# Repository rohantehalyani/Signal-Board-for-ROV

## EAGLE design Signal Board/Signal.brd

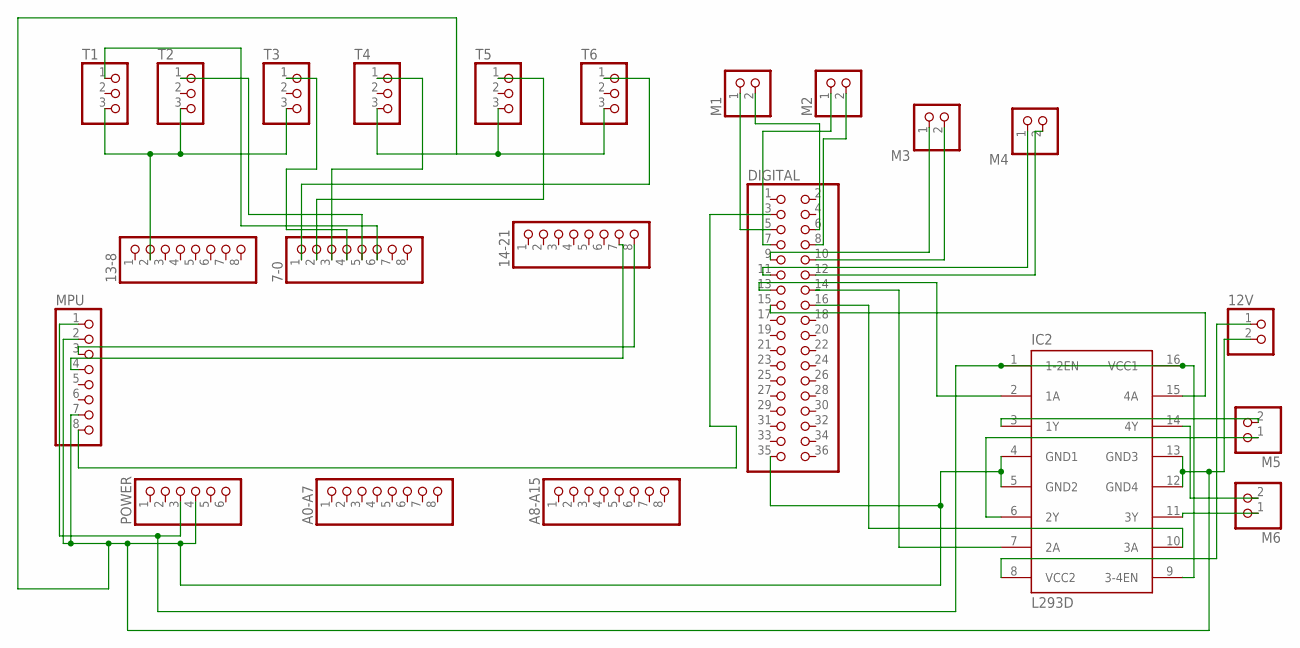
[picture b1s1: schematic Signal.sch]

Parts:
7-0, 13-8, 14-21: PINHD-1X8; 1X08
12V: PINHD-1X2; 1X02
A0-A7, A8-A15: PINHD-1X8; 1X08
DIGITAL: PINHD-2X18; 2X18
IC2: L293D; DIL16
M1, M2, M3, M4, M5, M6: PINHD-1X2; 1X02
MPU: PINHD-1X8; 1X08
POWER: PINHD-1X6; 1X06
T1, T2, T3, T4, T5, T6: PINHD-1X3; 1X03

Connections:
unnamed: DIGITAL.9, M3.1
unnamed: DIGITAL.10, M3.2
unnamed: DIGITAL.8, M2.2
unnamed: 7-0.1, T6.1
unnamed: 7-0.2, T5.1
unnamed: 7-0.3, T4.1
unnamed: 7-0.4, T3.1
unnamed: 7-0.5, T2.1
unnamed: DIGITAL.5, M1.1
unnamed: DIGITAL.6, M1.2
unnamed: DIGITAL.7, M2.1
unnamed: DIGITAL.11, M4.1
unnamed: DIGITAL.12, M4.2
unnamed: 12V.2, DIGITAL.35, IC2.4 (GND1), IC2.5 (GND2), IC2.12 (GND4), IC2.13 (GND3), MPU.2, MPU.7, POWER.4, T4.3, T5.3, T6.3
unnamed: DIGITAL.13, IC2.2 (1A)
unnamed: DIGITAL.14, IC2.7 (2A)
unnamed: DIGITAL.15, IC2.15 (4A)
unnamed: DIGITAL.16, IC2.10 (3A)
unnamed: IC2.1 (1-2EN), IC2.9 (3-4EN), IC2.16 (VCC1), MPU.1, POWER.3
unnamed: DIGITAL.3, MPU.8
unnamed: 7-0.6, T1.1
unnamed: 14-21.8, MPU.3
unnamed: 14-21.7, MPU.4
unnamed: 13-8.2, T1.3, T2.3, T3.3
unnamed: IC2.6 (2Y), M5.1
unnamed: 12V.1, IC2.8 (VCC2)
unnamed: IC2.14 (4Y), M6.2
unnamed: IC2.3 (1Y), M5.2
unnamed: IC2.11 (3Y), M6.1

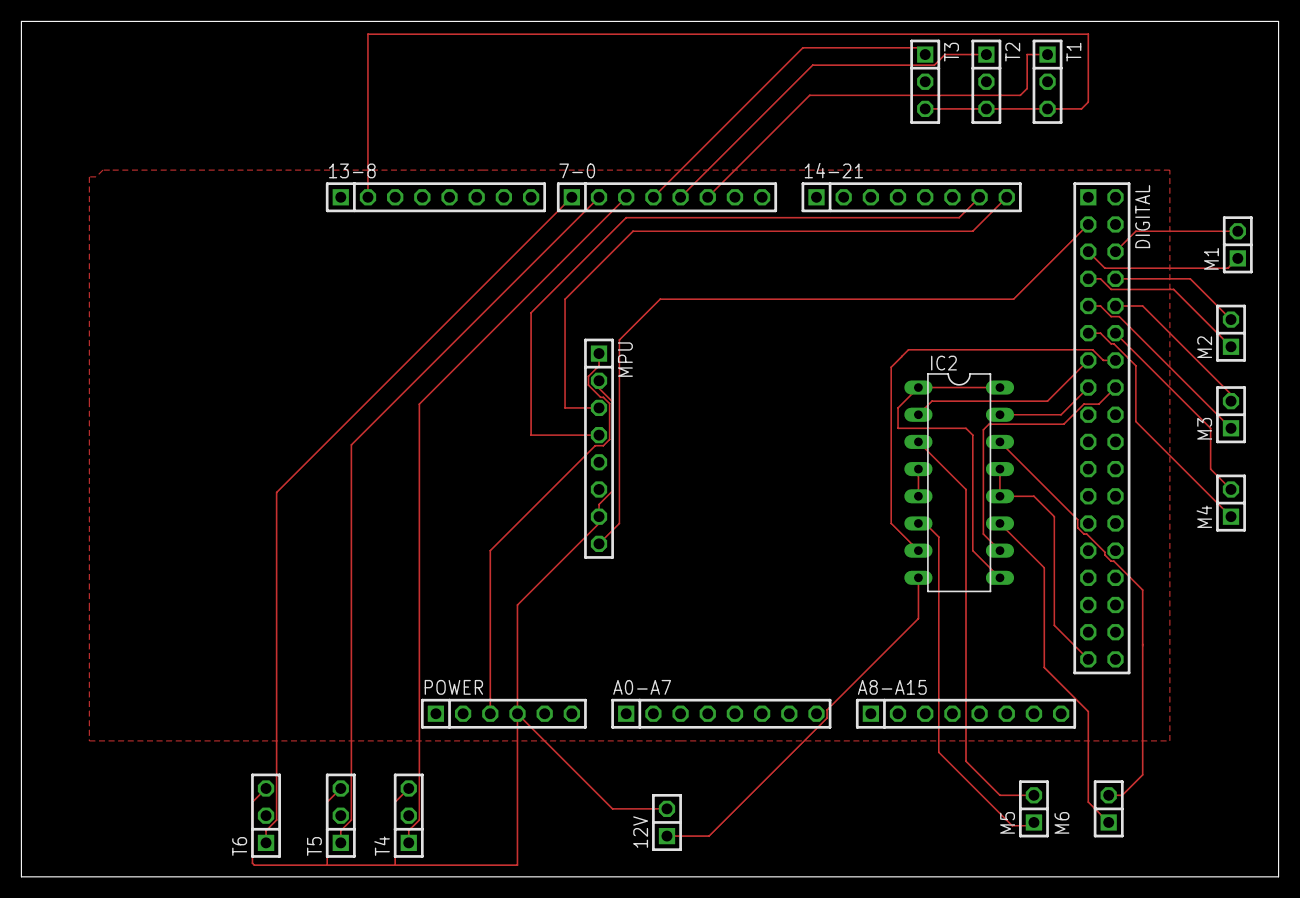
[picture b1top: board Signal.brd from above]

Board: 2 copper layers, 117.5 x 79.9 mm, 22 parts (0 on the bottom side), 29 nets.

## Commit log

2020-02-27 6ESC signal board
